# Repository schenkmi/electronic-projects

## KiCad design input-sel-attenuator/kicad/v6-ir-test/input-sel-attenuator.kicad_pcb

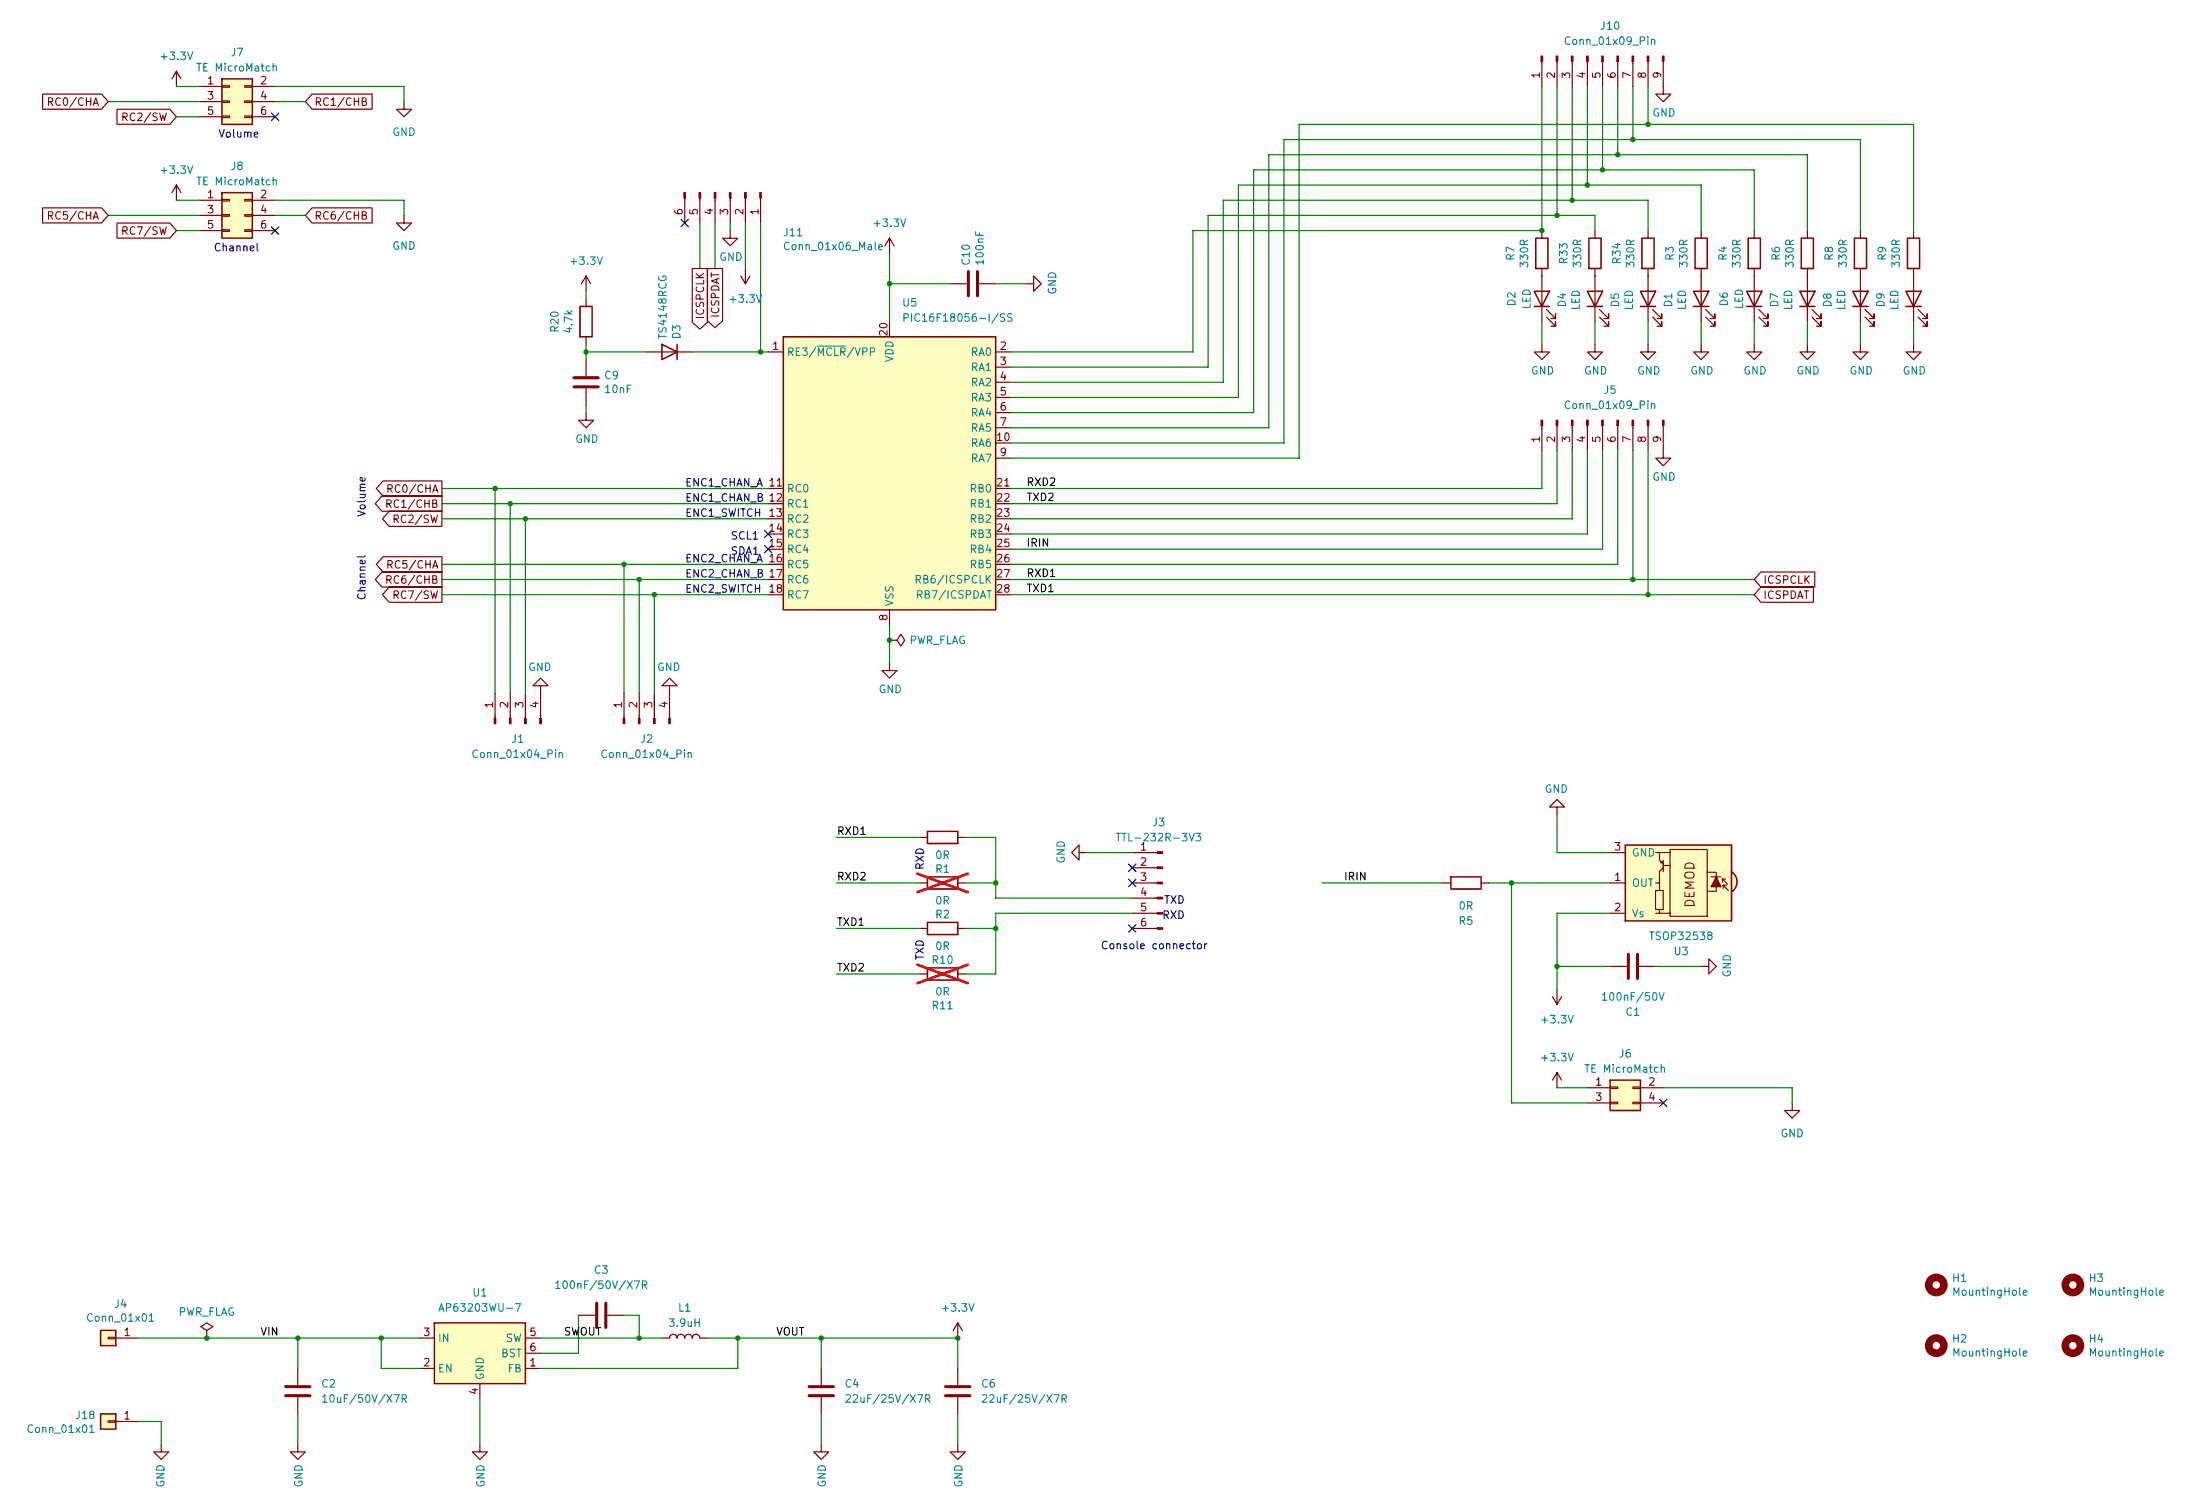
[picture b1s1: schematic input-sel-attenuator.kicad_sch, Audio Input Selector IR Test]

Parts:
C1: 100nF/50V; C_0603_1608Metric_Pad1.08x0.95mm_HandSolder
C2: 10uF/50V/X7R; C_1206_3216Metric_Pad1.33x1.80mm_HandSolder
C3: 100nF/50V/X7R; C_0603_1608Metric_Pad1.08x0.95mm_HandSolder
C4, C6: 22uF/25V/X7R; C_1210_3225Metric_Pad1.33x2.70mm_HandSolder
C9: 10nF; C_0603_1608Metric_Pad1.08x0.95mm_HandSolder
C10: 100nF; C_0603_1608Metric_Pad1.08x0.95mm_HandSolder
D1, D2, D4, D5, D6, D7, D8, D9: LED; LED_0603_1608Metric_Pad1.05x0.95mm_HandSolder
D3: TS4148RCG; D_0603_1608Metric_Pad1.05x0.95mm_HandSolder
H1, H2, H3, H4: MountingHole; MountingHole_3.2mm_M3_Pad_Via
J1, J2: Conn_01x04_Pin; PinHeader_1x04_P2.54mm_Vertical
J3: TTL-232R-3V3; PinHeader_1x06_P2.54mm_Vertical
J4, J18: Conn_01x01; Pin_D1.0mm_L10.0mm
J5, J10: Conn_01x09_Pin; PinHeader_1x09_P2.54mm_Vertical
J6: TE MicroMatch; TE_Micro-MaTch_215079-4_2x02_P1.27mm_Vertical
J7, J8: TE MicroMatch; TE_Micro-MaTch_215079-6_2x03_P1.27mm_Vertical
J11: Conn_01x06_Male; PinHeader_1x06_P2.54mm_Vertical
L1: 3.9uH; L_Bourns-SRN6028
R1, R5, R10: 0R; R_0603_1608Metric_Pad0.98x0.95mm_HandSolder
R2, R11: 0R; R_0603_1608Metric_Pad0.98x0.95mm_HandSolder; not fitted
R3, R4, R6, R7, R8, R9, R33, R34: 330R; R_0603_1608Metric_Pad0.98x0.95mm_HandSolder
R20: 4.7k; R_0603_1608Metric_Pad0.98x0.95mm_HandSolder
U1: AP63203WU-7; TSOT-23-6
U3: TSOP32538; Vishay_MOLD-3Pin
U5: PIC16F18056-I/SS; SOIC-28W_7.5x17.9mm_P1.27mm

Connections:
+3.3V: C1.2, C4.1, C6.1, C10.1, J6.1, J7.1, J8.1, J11.2, L1.2, R20.1, U1.1 (FB), U3.2 (Vs), U5.20 (VDD)
/IRIN: J5.5, R5.2, U5.25 (RB4)
/RXD2: J5.1, R2.1, U5.21 (RB0)
/SWOUT: C3.1, L1.1, U1.5 (SW)
/TXD2: J5.2, R11.1, U5.22 (RB1)
/VIN: C2.1, J4.1, U1.2 (EN), U1.3 (IN)
GND: C1.1, C2.2, C4.2, C6.2, C9.2, C10.2, D1.1 (K), D2.1 (K), D4.1 (K), D5.1 (K), D6.1 (K), D7.1 (K), D8.1 (K), D9.1 (K), J1.4, J2.4, J3.1, J5.9, J6.2, J7.2, J8.2, J10.9, J11.3, J18.1, U1.4 (GND), U3.3 (GND), U5.8 (VSS), U5.19 (VSS)
ICSPCLK: J5.7, J11.5, R1.1, U5.27 (RB6/ICSPCLK)
ICSPDAT: J5.8, J11.4, R10.1, U5.28 (RB7/ICSPDAT)
unnamed: D1.2 (A), R3.2
unnamed: D2.2 (A), R7.2
unnamed: C9.1, D3.2 (A), R20.2
unnamed: D3.1 (K), J11.1, U5.1 (RE3/~MCLR/VPP)
unnamed: D4.2 (A), R33.2
unnamed: D5.2 (A), R34.2
unnamed: D6.2 (A), R4.2
unnamed: D7.2 (A), R6.2
unnamed: D8.2 (A), R8.2
unnamed: D9.2 (A), R9.2
unnamed: J3.4, R1.2, R2.2
unnamed: J3.5, R10.2, R11.2
unnamed: J5.3, U5.23 (RB2)
unnamed: J5.4, U5.24 (RB3)
unnamed: J5.6, U5.26 (RB5)
unnamed: J6.3, R5.1, U3.1 (OUT)
unnamed: J10.1, R7.1, U5.2 (RA0)
unnamed: J10.2, R33.1, U5.3 (RA1)
unnamed: J10.3, R34.1, U5.4 (RA2)
unnamed: J10.4, R3.1, U5.5 (RA3)
unnamed: J10.5, R4.1, U5.6 (RA4)
unnamed: J10.6, R6.1, U5.7 (RA5)
unnamed: J10.7, R8.1, U5.10 (RA6)
unnamed: J10.8, R9.1, U5.9 (RA7)
unnamed: C3.2, U1.6 (BST)
RC0/CHA: J1.1, J7.3, U5.11 (RC0)
RC1/CHB: J1.2, J7.4, U5.12 (RC1)
RC2/SW: J1.3, J7.5, U5.13 (RC2)
RC5/CHA: J2.1, J8.3, U5.16 (RC5)
RC6/CHB: J2.2, J8.4, U5.17 (RC6)
RC7/SW: J2.3, J8.5, U5.18 (RC7)

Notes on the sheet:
TXD
SCL1
ENC2_CHAN_A
Channel
ENC2_SWITCH
ENC1_SWITCH
SDA1
ENC1_CHAN_A
RXD
Console connector
ENC1_CHAN_B
Volume
ENC2_CHAN_B

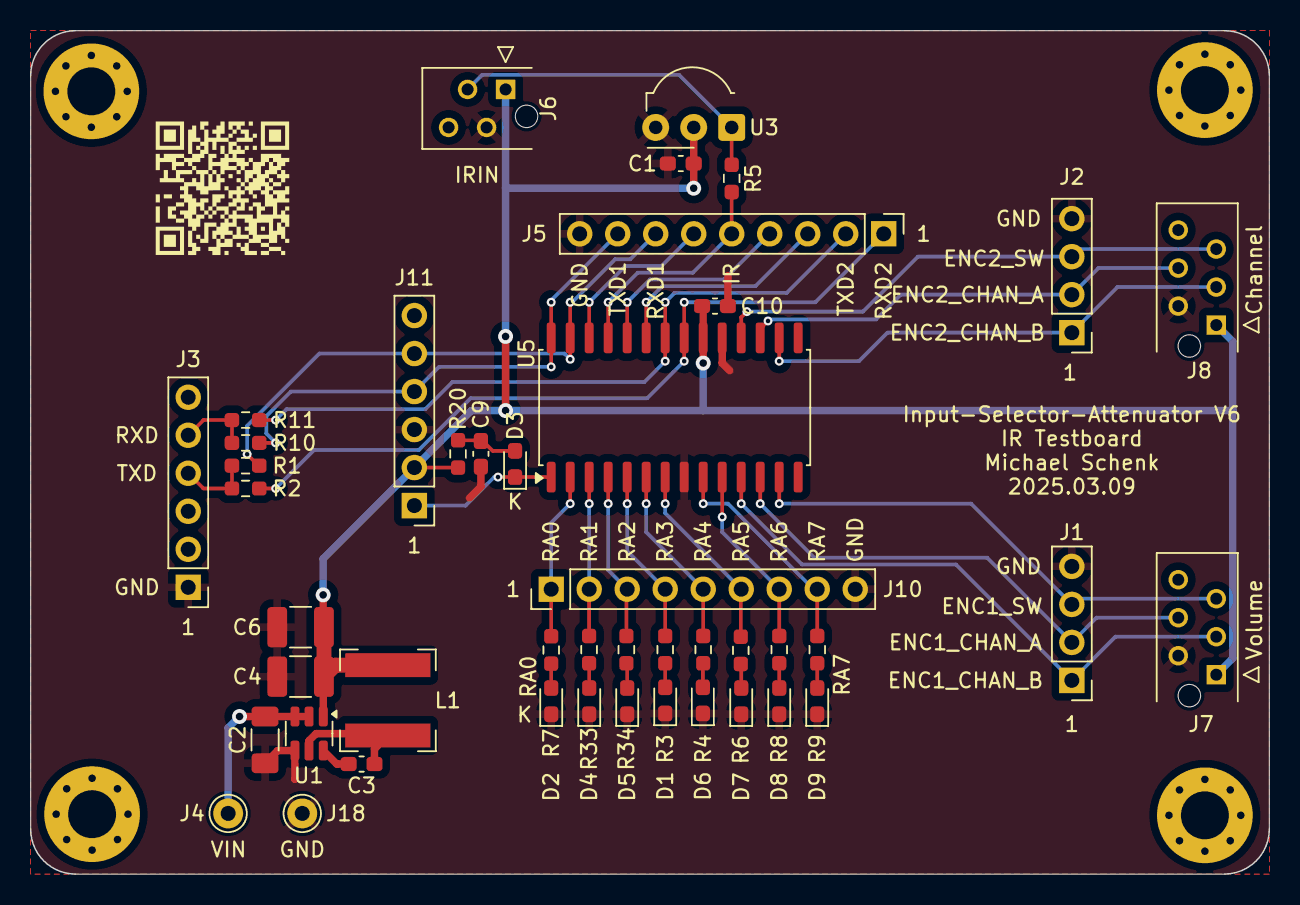
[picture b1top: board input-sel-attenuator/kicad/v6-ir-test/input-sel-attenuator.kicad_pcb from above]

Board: 2 copper layers, 82.8 x 56.4 mm, 49 parts (0 on the bottom side), 40 nets.

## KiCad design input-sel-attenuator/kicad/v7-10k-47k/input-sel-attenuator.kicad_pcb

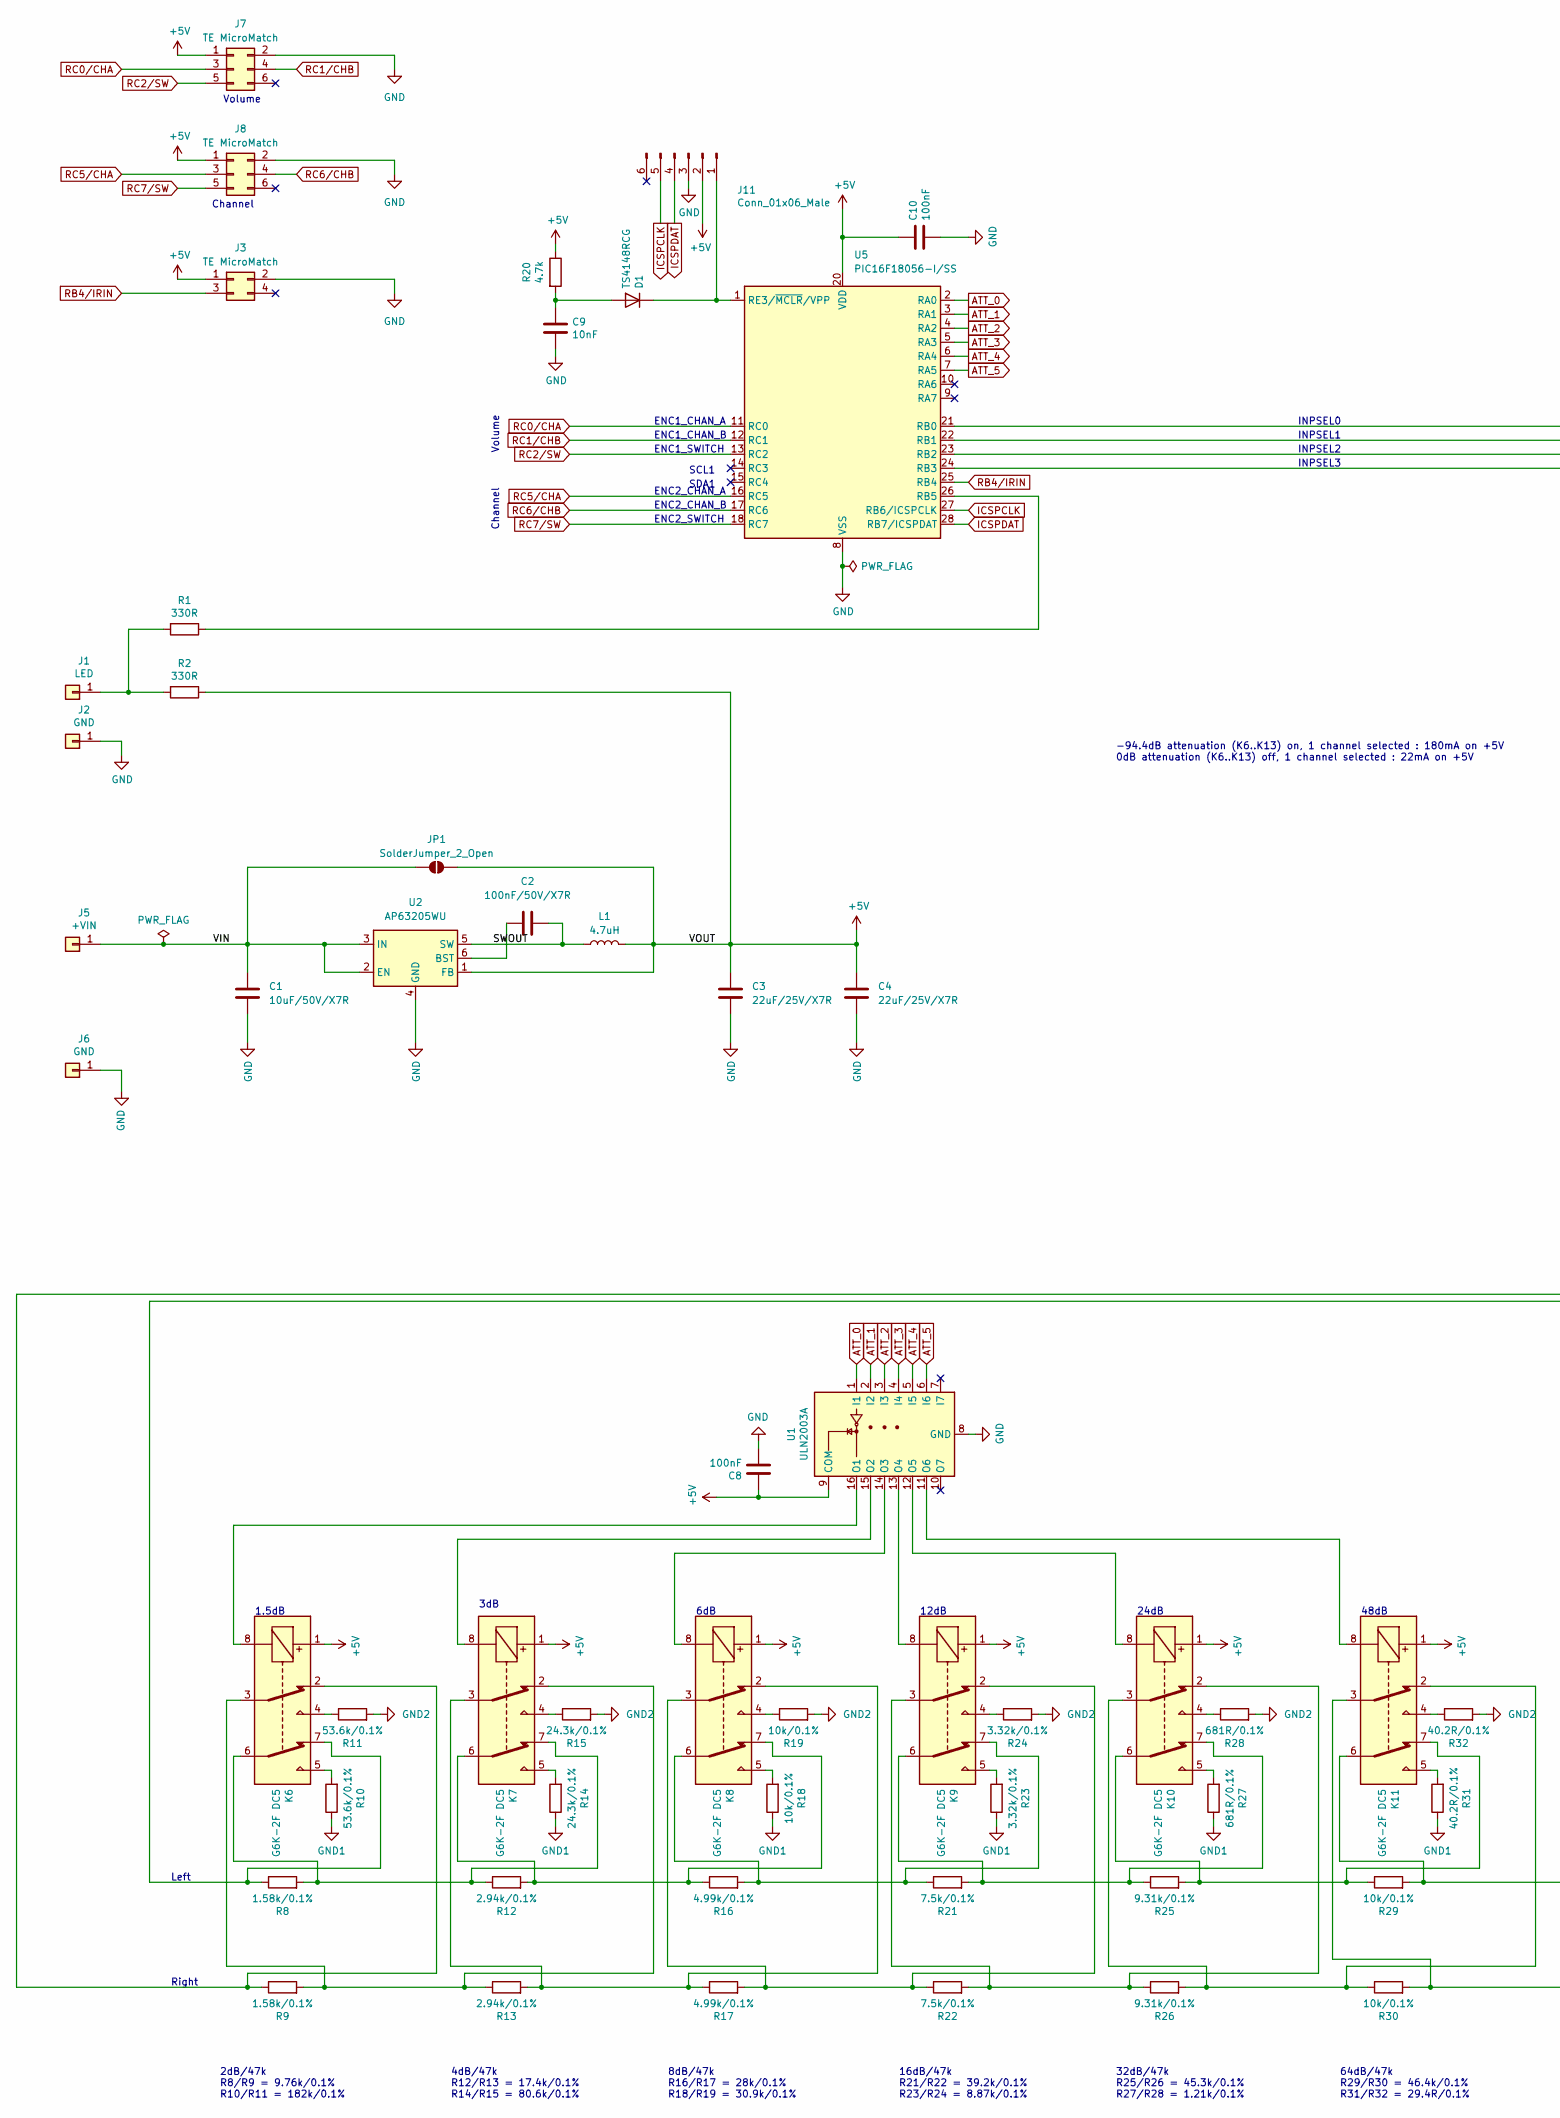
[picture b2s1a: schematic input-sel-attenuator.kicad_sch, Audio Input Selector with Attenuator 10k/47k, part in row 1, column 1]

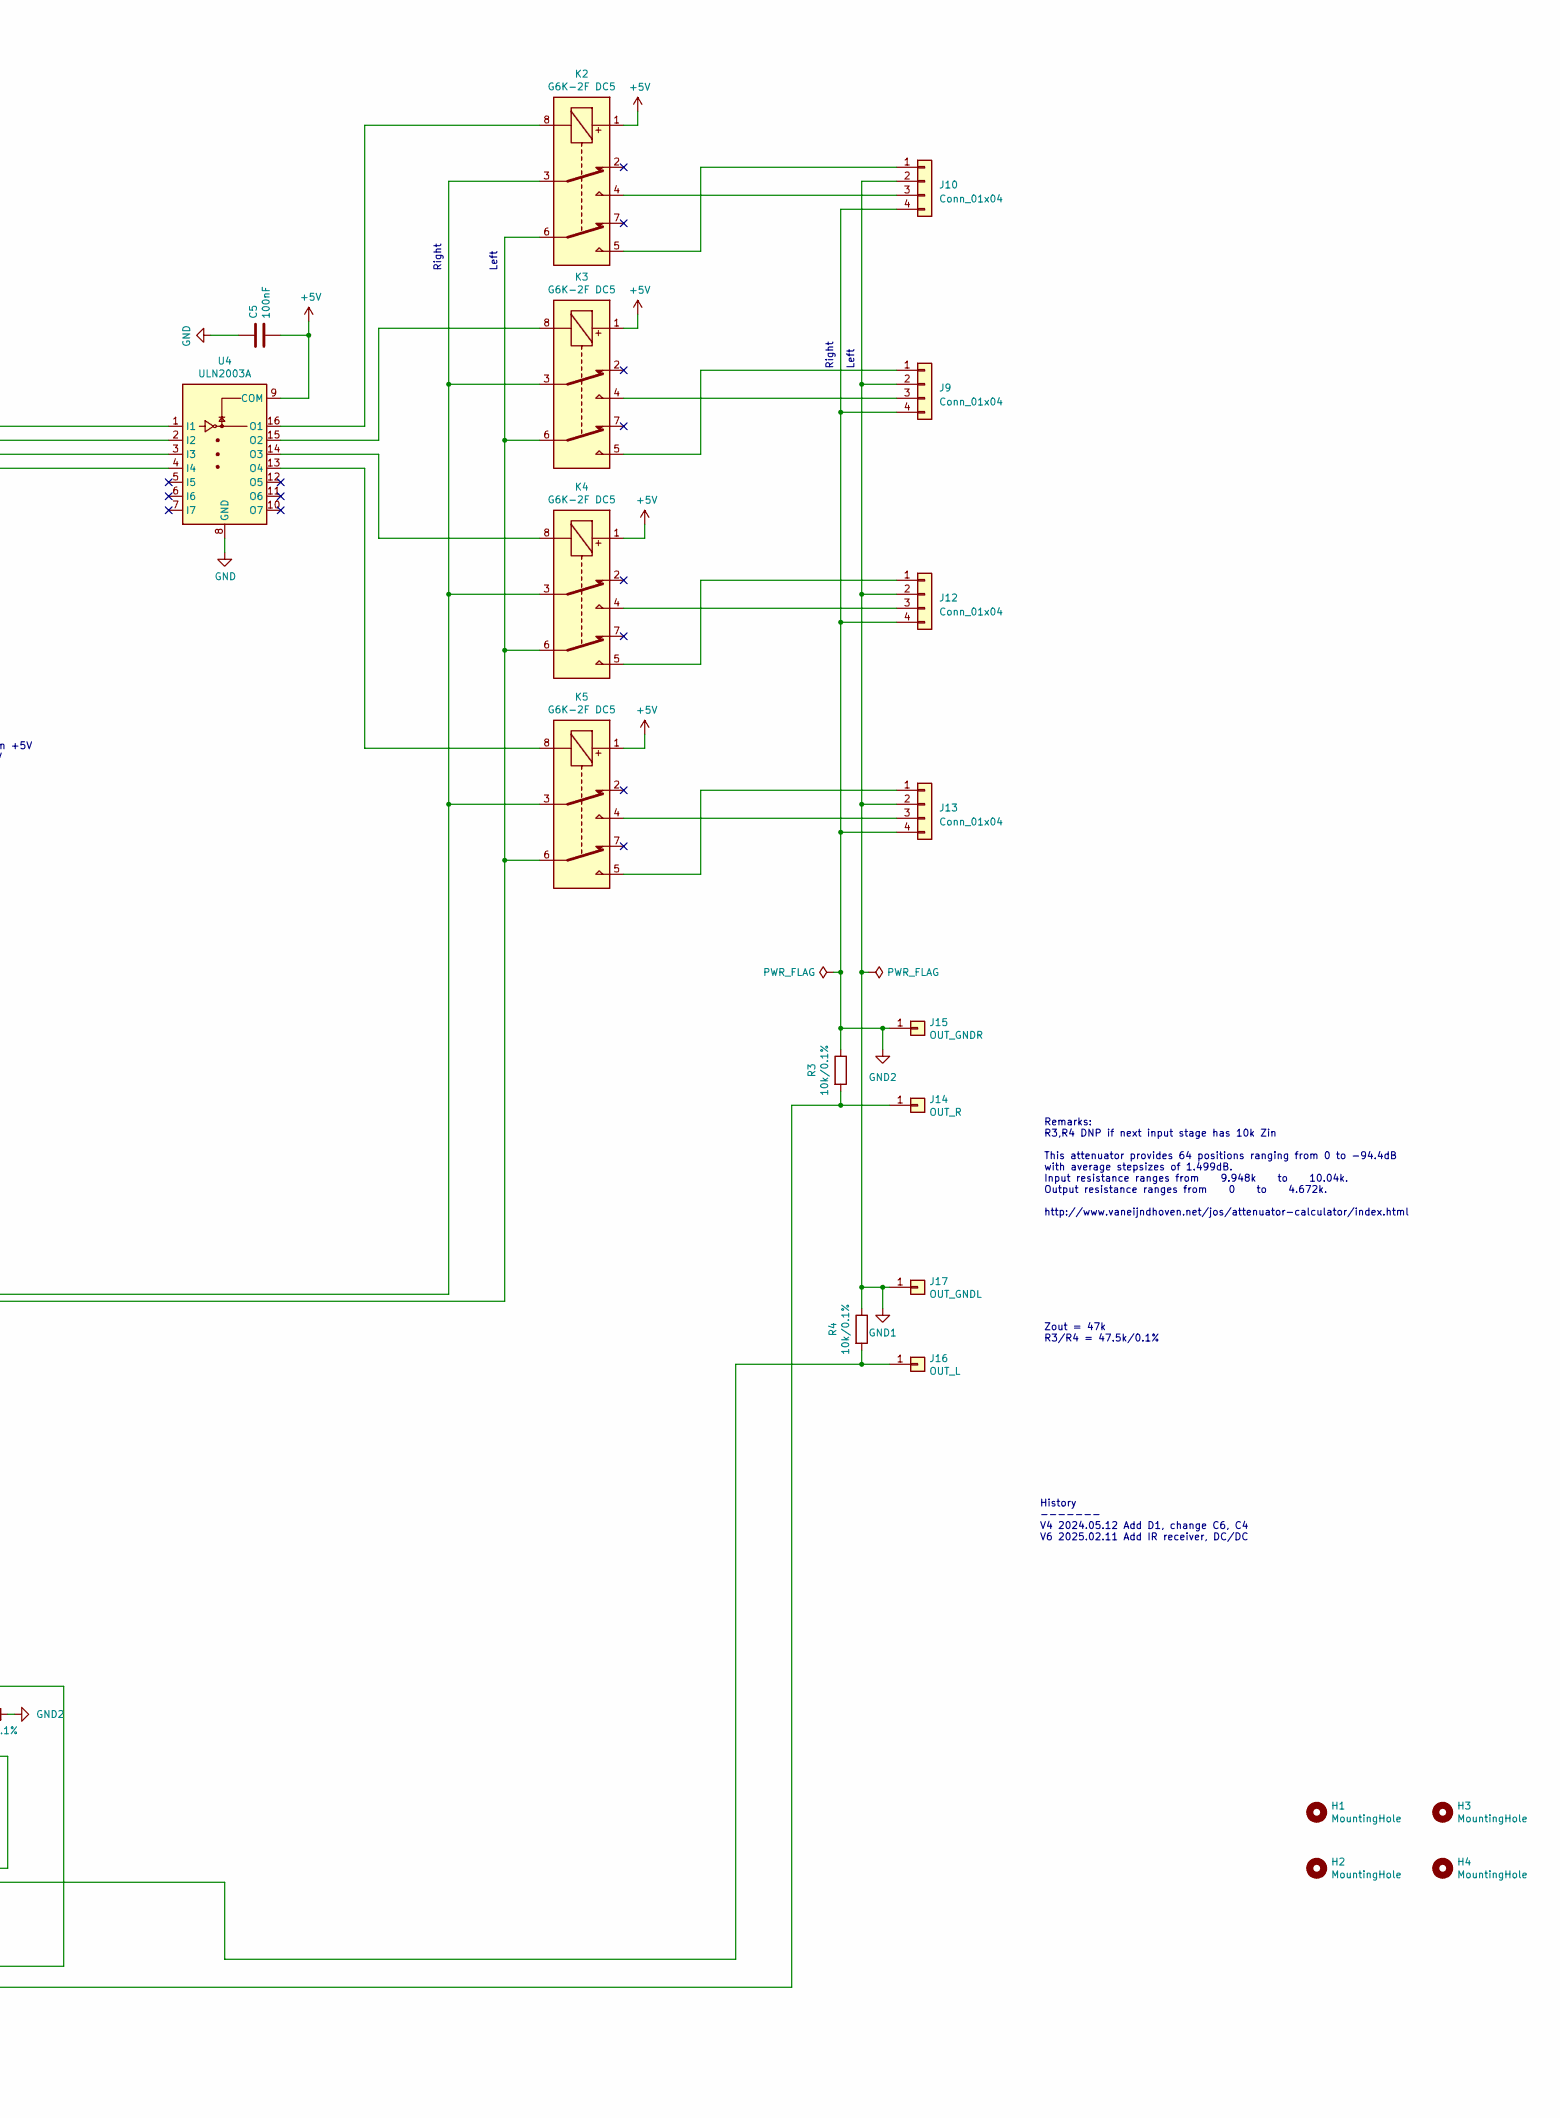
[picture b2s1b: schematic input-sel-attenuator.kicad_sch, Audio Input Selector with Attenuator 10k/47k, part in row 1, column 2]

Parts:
C1: 10uF/50V/X7R; C_1206_3216Metric_Pad1.33x1.80mm_HandSolder
C2: 100nF/50V/X7R; C_0603_1608Metric_Pad1.08x0.95mm_HandSolder
C3, C4: 22uF/25V/X7R; C_1210_3225Metric_Pad1.33x2.70mm_HandSolder
C5, C8, C10: 100nF; C_0805_2012Metric_Pad1.18x1.45mm_HandSolder
C9: 10nF; C_0805_2012Metric_Pad1.18x1.45mm_HandSolder
D1: TS4148RCG; D_0603_1608Metric_Pad1.05x0.95mm_HandSolder
H1, H4: MountingHole; MountingHole_3.2mm_M3_Pad_Via
H2, H3: MountingHole; MountingHole_3.2mm_M3
J1: LED; Pin_D1.0mm_L10.0mm
J2, J6: GND; Pin_D1.0mm_L10.0mm
J3: TE MicroMatch; TE_Micro-MaTch_215079-4_2x02_P1.27mm_Vertical
J5: +VIN; Pin_D1.0mm_L10.0mm
J7, J8: TE MicroMatch; TE_Micro-MaTch_215079-6_2x03_P1.27mm_Vertical
J9, J10, J12, J13: Conn_01x04; Hirose_DF13-04P-1.25DSA_1x04_P1.25mm_Vertical
J11: Conn_01x06_Male; PinHeader_1x06_P2.54mm_Vertical
J14: OUT_R; Pin_D1.0mm_L10.0mm
J15: OUT_GNDR; Pin_D1.0mm_L10.0mm
J16: OUT_L; Pin_D1.0mm_L10.0mm
J17: OUT_GNDL; Pin_D1.0mm_L10.0mm
JP1: SolderJumper_2_Open; SolderJumper-2_P1.3mm_Open_Pad1.0x1.5mm
K2, K3, K4, K5, K6, K7, K8, K9, K10, K11: G6K-2F DC5; Relay_DPDT_Omron_G6K-2F
L1: 4.7uH; L_Bourns-SRN6028
R1, R2: 330R; R_0805_2012Metric_Pad1.20x1.40mm_HandSolder
R3, R4, R18, R19, R29, R30: 10k/0.1%; R_0805_2012Metric_Pad1.20x1.40mm_HandSolder
R8, R9: 1.58k/0.1%; R_0805_2012Metric_Pad1.20x1.40mm_HandSolder
R10, R11: 53.6k/0.1%; R_0805_2012Metric_Pad1.20x1.40mm_HandSolder
R12, R13: 2.94k/0.1%; R_0805_2012Metric_Pad1.20x1.40mm_HandSolder
R14, R15: 24.3k/0.1%; R_0805_2012Metric_Pad1.20x1.40mm_HandSolder
R16, R17: 4.99k/0.1%; R_0805_2012Metric_Pad1.20x1.40mm_HandSolder
R20: 4.7k; R_0805_2012Metric_Pad1.20x1.40mm_HandSolder
R21, R22: 7.5k/0.1%; R_0805_2012Metric_Pad1.20x1.40mm_HandSolder
R23, R24: 3.32k/0.1%; R_0805_2012Metric_Pad1.20x1.40mm_HandSolder
R25, R26: 9.31k/0.1%; R_0805_2012Metric_Pad1.20x1.40mm_HandSolder
R27, R28: 681R/0.1%; R_0805_2012Metric_Pad1.20x1.40mm_HandSolder
R31, R32: 40.2R/0.1%; R_0805_2012Metric_Pad1.20x1.40mm_HandSolder
U1, U4: ULN2003A; SOIC-16_3.9x9.9mm_P1.27mm
U2: AP63205WU; TSOT-23-6
U5: PIC16F18056-I/SS; SSOP-28_5.3x10.2mm_P0.65mm

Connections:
+5V: C3.1, C4.1, C5.2, C8.1, C10.1, J3.1, J7.1, J8.1, J11.2, JP1.2 (B), K2.1, K3.1, K4.1, K5.1, K6.1, K7.1, K8.1, K9.1, K10.1, K11.1, L1.2, R2.1, R20.1, U1.9 (COM), U2.1 (FB), U4.9 (COM), U5.20 (VDD)
/SWOUT: C2.1, L1.1, U2.5 (SW)
/VIN: C1.1, J5.1, JP1.1 (A), U2.2 (EN), U2.3 (IN)
ATT_0: U1.1 (I1), U5.2 (RA0)
ATT_1: U1.2 (I2), U5.3 (RA1)
ATT_2: U1.3 (I3), U5.4 (RA2)
ATT_3: U1.4 (I4), U5.5 (RA3)
ATT_4: U1.5 (I5), U5.6 (RA4)
ATT_5: U1.6 (I6), U5.7 (RA5)
GND: C1.2, C3.2, C4.2, C5.1, C8.2, C9.2, C10.2, J2.1, J3.2, J6.1, J7.2, J8.2, J11.3, U1.8 (GND), U2.4 (GND), U4.8 (GND), U5.8 (VSS), U5.19 (VSS)
GND1: J9.2, J10.2, J12.2, J13.2, J17.1, R4.1, R10.1, R14.1, R18.1, R23.1, R27.1, R31.1
GND2: J9.4, J10.4, J12.4, J13.4, J15.1, R3.1, R11.2, R15.2, R19.2, R24.2, R28.2, R32.2
ICSPCLK: J11.5, U5.27 (RB6/ICSPCLK)
ICSPDAT: J11.4, U5.28 (RB7/ICSPDAT)
unnamed: C9.1, D1.2 (A), R20.2
unnamed: D1.1 (K), J11.1, U5.1 (RE3/~MCLR/VPP)
unnamed: J1.1, R1.2, R2.2
unnamed: J9.1, K3.5
unnamed: J9.3, K3.4
unnamed: J10.1, K2.5
unnamed: J10.3, K2.4
unnamed: J12.1, K4.5
unnamed: J12.3, K4.4
unnamed: J13.1, K5.5
unnamed: J13.3, K5.4
unnamed: J14.1, K11.3, R3.2, R30.2
unnamed: J16.1, K11.6, R4.2, R29.2
unnamed: K2.3, K3.3, K4.3, K5.3, K6.2, R9.1
unnamed: K2.6, K3.6, K4.6, K5.6, K6.7, R8.1
unnamed: K6.3, K7.2, R9.2, R13.1
unnamed: K6.4, R11.1
unnamed: K6.5, R10.2
unnamed: K6.6, K7.7, R8.2, R12.1
unnamed: K7.3, K8.2, R13.2, R17.1
unnamed: K7.4, R15.1
unnamed: K7.5, R14.2
unnamed: K7.6, K8.7, R12.2, R16.1
unnamed: K8.3, K9.2, R17.2, R22.1
unnamed: K8.4, R19.1
unnamed: K8.5, R18.2
unnamed: K8.6, K9.7, R16.2, R21.1
unnamed: K9.4, R24.1
unnamed: K9.5, R23.2
unnamed: K9.3, K10.2, R22.2, R26.1
unnamed: K10.3, K11.2, R26.2, R30.1
unnamed: K10.4, R28.1
unnamed: K10.5, R27.2
unnamed: K10.6, K11.7, R25.2, R29.1
unnamed: K9.6, K10.7, R21.2, R25.1
unnamed: K11.4, R32.1
unnamed: K11.5, R31.2
unnamed: K6.8, U1.16 (O1)
unnamed: K7.8, U1.15 (O2)
unnamed: K8.8, U1.14 (O3)
unnamed: K9.8, U1.13 (O4)
unnamed: K10.8, U1.12 (O5)
unnamed: K11.8, U1.11 (O6)
unnamed: C2.2, U2.6 (BST)
unnamed: U4.1 (I1), U5.21 (RB0)
unnamed: U4.2 (I2), U5.22 (RB1)
unnamed: U4.3 (I3), U5.23 (RB2)
unnamed: U4.4 (I4), U5.24 (RB3)
unnamed: K2.8, U4.16 (O1)
unnamed: K3.8, U4.15 (O2)
unnamed: K4.8, U4.14 (O3)
unnamed: K5.8, U4.13 (O4)
unnamed: R1.1, U5.26 (RB5)
RB4/IRIN: J3.3, U5.25 (RB4)
RC0/CHA: J7.3, U5.11 (RC0)
RC1/CHB: J7.4, U5.12 (RC1)
RC2/SW: J7.5, U5.13 (RC2)
RC5/CHA: J8.3, U5.16 (RC5)
RC6/CHB: J8.4, U5.17 (RC6)
RC7/SW: J8.5, U5.18 (RC7)

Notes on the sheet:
Right
6dB
24dB
32dB/47k R25/R26 = 45.3k/0.1% R27/R28 = 1.21k/0.1%
INPSEL3
SCL1
History ------- V4 2024.05.12 Add D1, change C6, C4 V6 2025.02.11 Add IR receiver, DC/DC
ENC2_CHAN_A
Channel
8dB/47k R16/R17 = 28k/0.1% R18/R19 = 30.9k/0.1%
Left
3dB
ENC2_SWITCH
12dB
ENC1_SWITCH
SDA1
INPSEL0
ENC1_CHAN_A
2dB/47k R8/R9 = 9.76k/0.1% R10/R11 = 182k/0.1%
16dB/47k R21/R22 = 39.2k/0.1% R23/R24 = 8.87k/0.1%
4dB/47k R12/R13 = 17.4k/0.1% R14/R15 = 80.6k/0.1%
64dB/47k R29/R30 = 46.4k/0.1% R31/R32 = 29.4R/0.1%
Remarks: R3,R4 DNP if next input stage has 10k Zin This attenuator provides 64 positions ranging from 0 to -94.4dB with average stepsizes of 1.499dB. Input resistance ranges from 9.948k to 10.04k. Output resistance ranges from 0 to 4.672k. http://www.vaneijndhoven.net/jos/attenuator-calculator/inde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
1.5dB
ENC1_CHAN_B
48dB
Volume
-94.4dB attenuation (K6..K13) on, 1 channel selected : 180mA on +5V 0dB attenuation (K6..K13) off, 1 channel selected : 22mA on +5V
ENC2_CHAN_B
INPSEL1
INPSEL2
Zout = 47k R3/R4 = 47.5k/0.1%

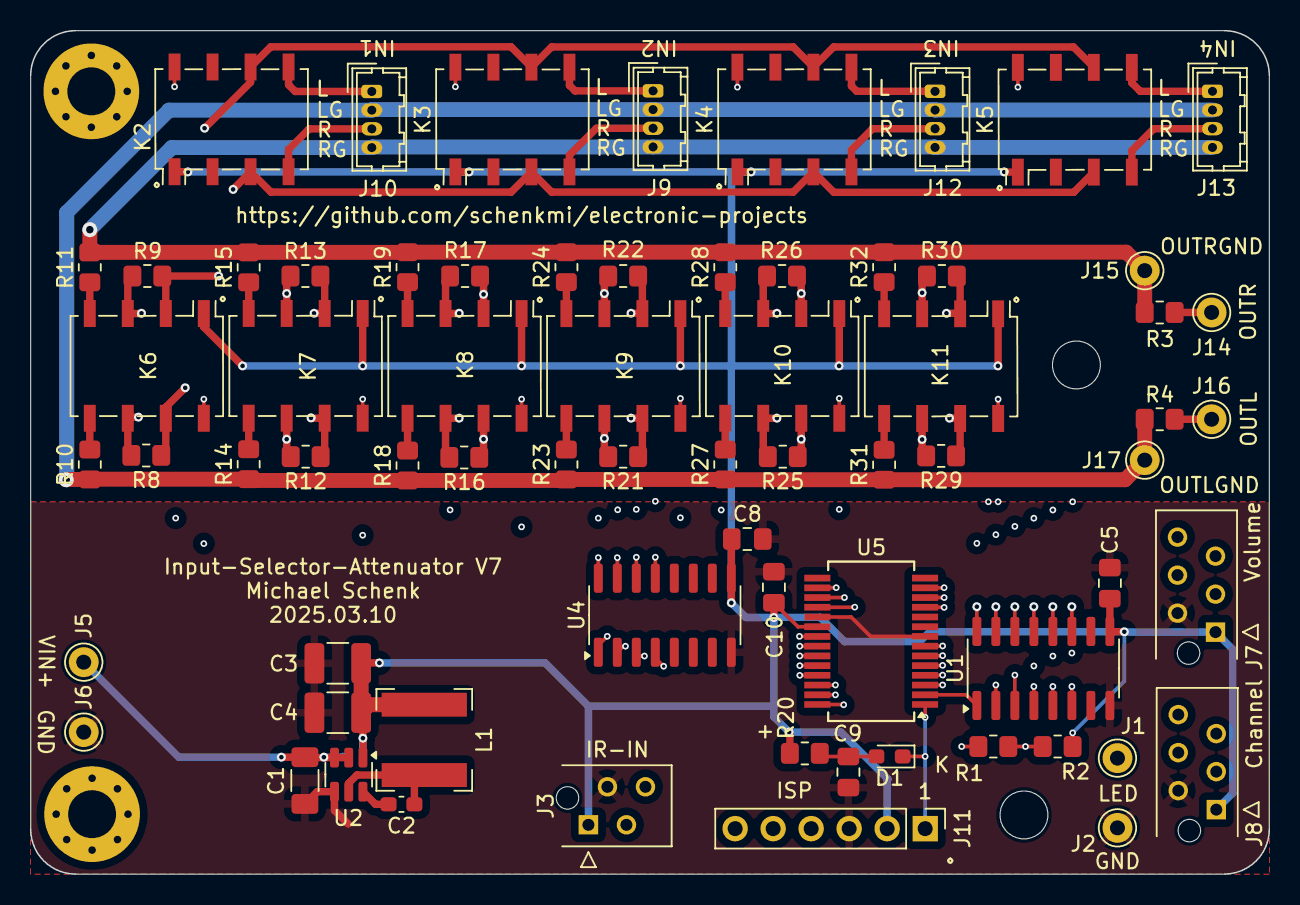
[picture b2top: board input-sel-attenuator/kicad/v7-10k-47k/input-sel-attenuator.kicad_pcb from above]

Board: 4 copper layers, 82.8 x 56.4 mm, 74 parts (1 on the bottom side), 74 nets.

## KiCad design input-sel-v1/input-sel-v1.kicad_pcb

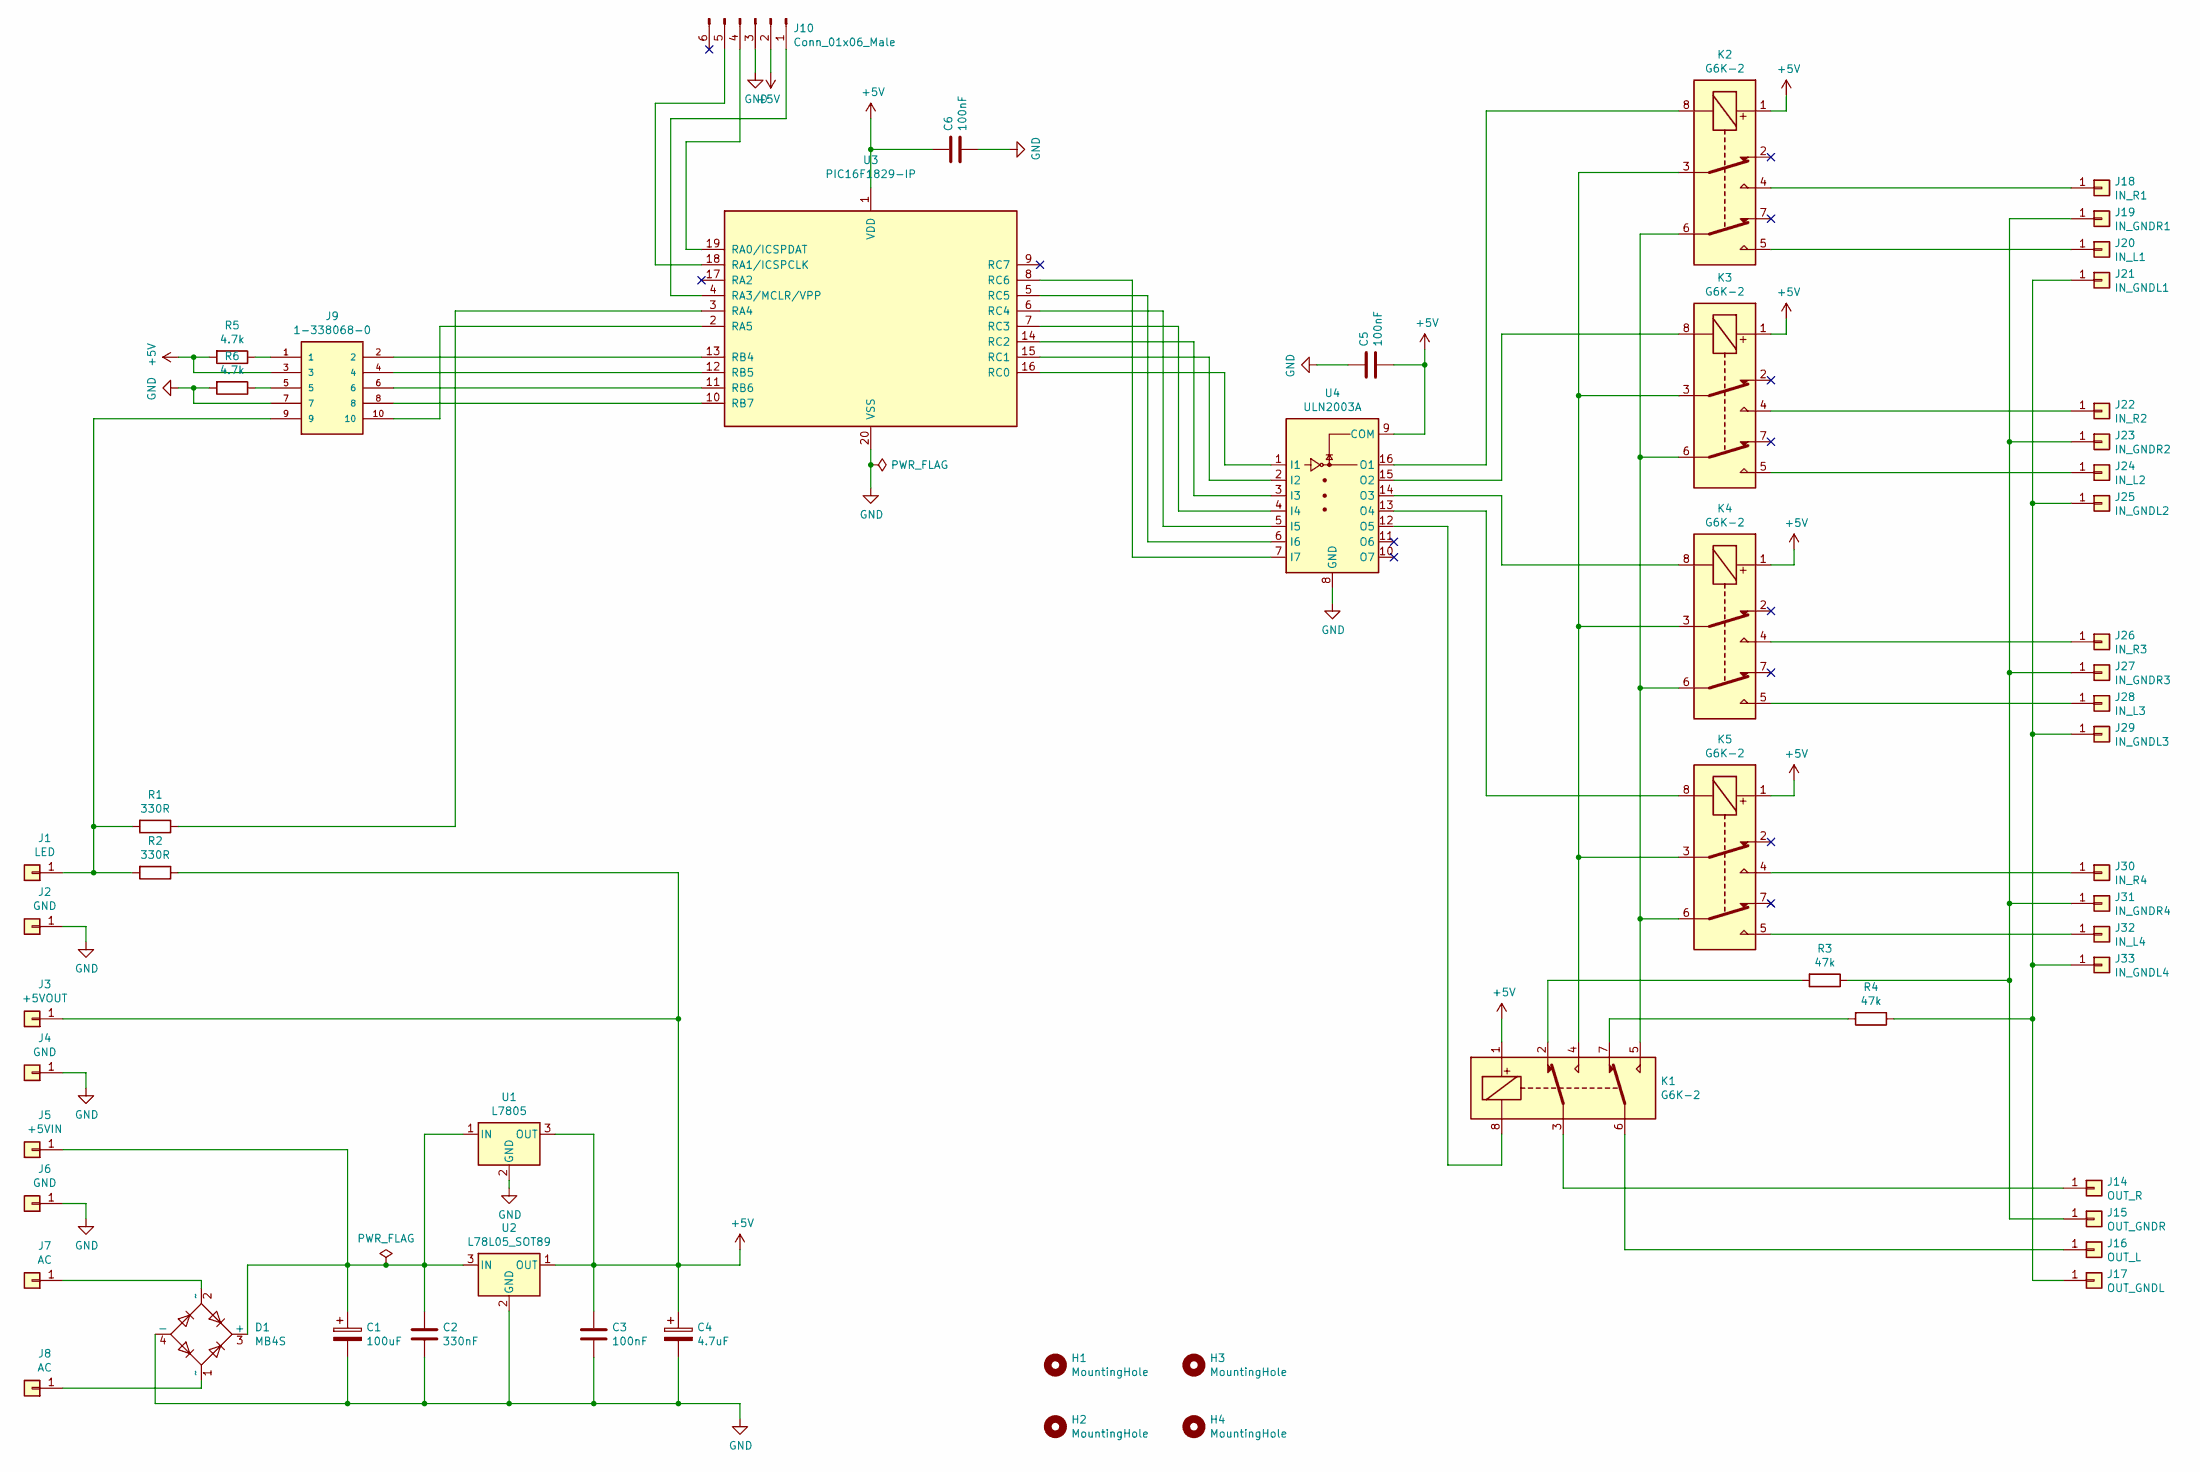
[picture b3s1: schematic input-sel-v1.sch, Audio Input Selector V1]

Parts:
C1: 100uF; CP_Elec_8x10
C2: 330nF; C_0805_2012Metric_Pad1.18x1.45mm_HandSolder
C3, C5, C6: 100nF; C_0805_2012Metric_Pad1.18x1.45mm_HandSolder
C4: 4.7uF; CP_Elec_4x4.5
D1: MB4S; TO-269AA
H1, H2, H3, H4: MountingHole; MountingHole_3.2mm_M3
J1: LED; Pin_D1.0mm_L10.0mm
J2, J4, J6: GND; Pin_D1.0mm_L10.0mm
J3: +5VOUT; Pin_D1.0mm_L10.0mm
J5: +5VIN; Pin_D1.0mm_L10.0mm
J7, J8: AC; Pin_D1.0mm_L10.0mm
J9: 1-338068-0; TE_1-338068-0
J10: Conn_01x06_Male; PinHeader_1x06_P2.54mm_Vertical
J14: OUT_R; Pin_D1.0mm_L10.0mm
J15: OUT_GNDR; Pin_D1.0mm_L10.0mm
J16: OUT_L; Pin_D1.0mm_L10.0mm
J17: OUT_GNDL; Pin_D1.0mm_L10.0mm
J18: IN_R1; Pin_D1.0mm_L10.0mm
J19: IN_GNDR1; Pin_D1.0mm_L10.0mm
J20: IN_L1; Pin_D1.0mm_L10.0mm
J21: IN_GNDL1; Pin_D1.0mm_L10.0mm
J22: IN_R2; Pin_D1.0mm_L10.0mm
J23: IN_GNDR2; Pin_D1.0mm_L10.0mm
J24: IN_L2; Pin_D1.0mm_L10.0mm
J25: IN_GNDL2; Pin_D1.0mm_L10.0mm
J26: IN_R3; Pin_D1.0mm_L10.0mm
J27: IN_GNDR3; Pin_D1.0mm_L10.0mm
J28: IN_L3; Pin_D1.0mm_L10.0mm
J29: IN_GNDL3; Pin_D1.0mm_L10.0mm
J30: IN_R4; Pin_D1.0mm_L10.0mm
J31: IN_GNDR4; Pin_D1.0mm_L10.0mm
J32: IN_L4; Pin_D1.0mm_L10.0mm
J33: IN_GNDL4; Pin_D1.0mm_L10.0mm
K1, K2, K3, K4, K5: G6K-2; Relay_DPDT_Omron_G6K-2F
R1, R2: 330R; R_0805_2012Metric_Pad1.20x1.40mm_HandSolder
R3, R4: 47k; R_0805_2012Metric_Pad1.20x1.40mm_HandSolder
R5, R6: 4.7k; R_0805_2012Metric_Pad1.20x1.40mm_HandSolder
U1: L7805; TO-220-3_Vertical
U2: L78L05_SOT89; SOT-89-3
U3: PIC16F1829-IP; DIP-20_W7.62mm
U4: ULN2003A; SOIC-16_3.9x9.9mm_P1.27mm

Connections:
+5V: C3.1, C4.1, C5.2, C6.1, J3.1, J9.3, J10.2, K1.1, K2.1, K3.1, K4.1, K5.1, R2.1, R5.2, U1.3 (OUT), U2.1 (OUT), U3.1 (VDD), U4.9 (COM)
GND: C1.2, C2.2, C3.2, C4.2, C5.1, C6.2, D1.4 (-), J2.1, J4.1, J6.1, J9.7, J10.3, R6.2, U1.2 (GND), U2.2 (GND), U3.20 (VSS), U4.8 (GND)
unnamed: C1.1, C2.1, D1.3 (+), J5.1, U1.1 (IN), U2.3 (IN)
unnamed: D1.1 (~~), J8.1
unnamed: D1.2 (~~), J7.1
unnamed: J1.1, J9.9, R1.2, R2.2
unnamed: J9.1, R5.1
unnamed: J9.2, U3.13 (RB4)
unnamed: J9.4, U3.12 (RB5)
unnamed: J9.5, R6.1
unnamed: J9.6, U3.11 (RB6)
unnamed: J9.8, U3.10 (RB7)
unnamed: J9.10, U3.2 (RA5)
unnamed: J10.1, U3.4 (RA3/MCLR/VPP)
unnamed: J10.4, U3.19 (RA0/ICSPDAT)
unnamed: J10.5, U3.18 (RA1/ICSPCLK)
unnamed: J14.1, K1.3
unnamed: J15.1, J19.1, J23.1, J27.1, J31.1, R3.1
unnamed: J16.1, K1.6
unnamed: J17.1, J21.1, J25.1, J29.1, J33.1, R4.1
unnamed: J18.1, K2.4
unnamed: J20.1, K2.5
unnamed: J22.1, K3.4
unnamed: J24.1, K3.5
unnamed: J26.1, K4.4
unnamed: J28.1, K4.5
unnamed: J30.1, K5.4
unnamed: J32.1, K5.5
unnamed: K1.2, R3.2
unnamed: K1.4, K2.3, K3.3, K4.3, K5.3
unnamed: K1.5, K2.6, K3.6, K4.6, K5.6
unnamed: K1.7, R4.2
unnamed: K1.8, U4.12 (O5)
unnamed: K2.8, U4.16 (O1)
unnamed: K3.8, U4.15 (O2)
unnamed: K4.8, U4.14 (O3)
unnamed: K5.8, U4.13 (O4)
unnamed: R1.1, U3.3 (RA4)
unnamed: U3.5 (RC5), U4.6 (I6)
unnamed: U3.6 (RC4), U4.5 (I5)
unnamed: U3.7 (RC3), U4.4 (I4)
unnamed: U3.8 (RC6), U4.7 (I7)
unnamed: U3.14 (RC2), U4.3 (I3)
unnamed: U3.15 (RC1), U4.2 (I2)
unnamed: U3.16 (RC0), U4.1 (I1)

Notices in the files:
input-sel-v1a/software/input-sel.X/mcc_generated_files/pin_manager.h:
(c) 2018 Microchip Technology Inc. and its subsidiaries.
